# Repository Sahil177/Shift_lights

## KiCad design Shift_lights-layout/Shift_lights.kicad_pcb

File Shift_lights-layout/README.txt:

There are two files in this folder of interest. The Shift_lights.pro which u can open in Kicad to view the full PCB layout and LED-PCB_dimentions.pdf to get detailed schematics on the layout

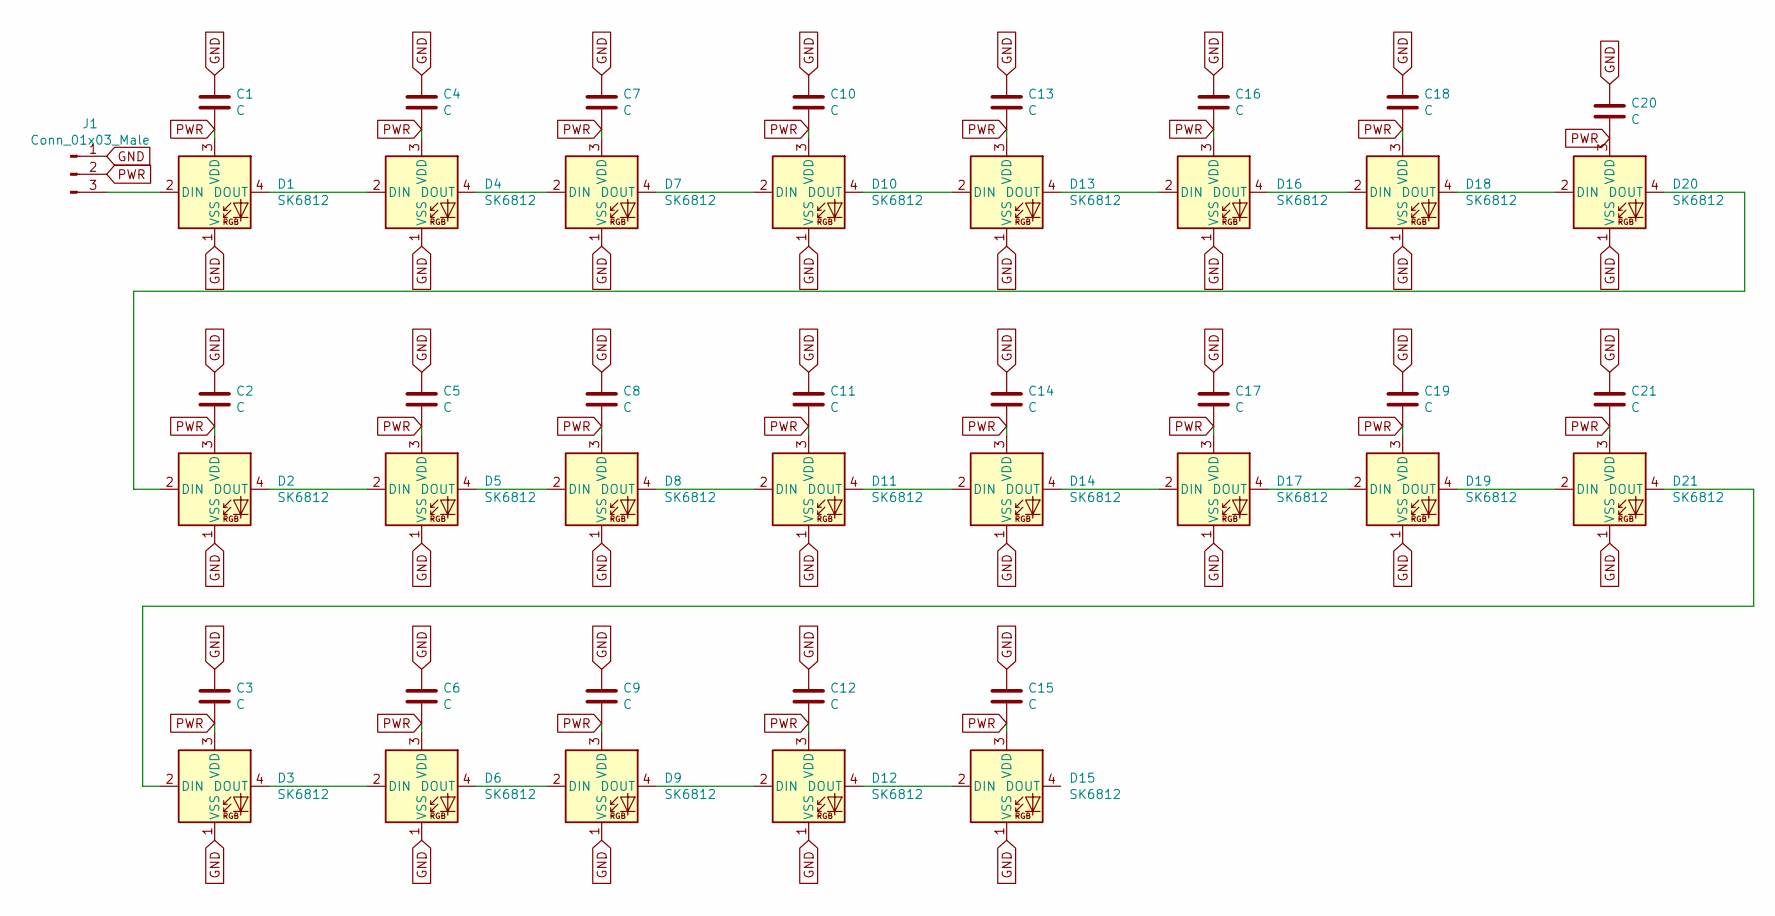
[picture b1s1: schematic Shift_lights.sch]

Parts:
C1, C2, C3, C4, C5, C6, C7, C8, C9, C10, C11, C12, C13, C14, C15, C16, C17, C18, C19, C20, C21: C; C0603C105K8PACTU
D1, D2, D3, D4, D5, D6, D7, D8, D9, D10, D11, D12, D13, D14, D15, D16, D17, D18, D19, D20, D21: SK6812; LED_SK6812_PLCC4_5.0x5.0mm_P3.2mm
J1: Conn_01x03_Male; 3_pin_connector

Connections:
GND: C1.1, C2.1, C3.1, C4.1, C5.1, C6.1, C7.1, C8.1, C9.1, C10.1, C11.1, C12.1, C13.1, C14.1, C15.1, C16.1, C17.1, C18.1, C19.1, C20.1, C21.1, D1.1 (VSS), D2.1 (VSS), D3.1 (VSS), D4.1 (VSS), D5.1 (VSS), D6.1 (VSS), D7.1 (VSS), D8.1 (VSS), D9.1 (VSS), D10.1 (VSS), D11.1 (VSS), D12.1 (VSS), D13.1 (VSS), D14.1 (VSS), D15.1 (VSS), D16.1 (VSS), D17.1 (VSS), D18.1 (VSS), D19.1 (VSS), D20.1 (VSS), D21.1 (VSS), J1.1
unnamed: D1.2 (DIN), J1.3
unnamed: D1.4 (DOUT), D4.2 (DIN)
unnamed: D2.2 (DIN), D20.4 (DOUT)
unnamed: D2.4 (DOUT), D5.2 (DIN)
unnamed: D3.4 (DOUT), D6.2 (DIN)
unnamed: D4.4 (DOUT), D7.2 (DIN)
unnamed: D5.4 (DOUT), D8.2 (DIN)
unnamed: D6.4 (DOUT), D9.2 (DIN)
unnamed: D7.4 (DOUT), D10.2 (DIN)
unnamed: D10.4 (DOUT), D13.2 (DIN)
unnamed: D8.4 (DOUT), D11.2 (DIN)
unnamed: D11.4 (DOUT), D14.2 (DIN)
unnamed: D9.4 (DOUT), D12.2 (DIN)
unnamed: D12.4 (DOUT), D15.2 (DIN)
unnamed: D13.4 (DOUT), D16.2 (DIN)
unnamed: D14.4 (DOUT), D17.2 (DIN)
unnamed: D16.4 (DOUT), D18.2 (DIN)
unnamed: D17.4 (DOUT), D19.2 (DIN)
unnamed: D18.4 (DOUT), D20.2 (DIN)
unnamed: D19.4 (DOUT), D21.2 (DIN)
unnamed: D3.2 (DIN), D21.4 (DOUT)
PWR: C1.2, C2.2, C3.2, C4.2, C5.2, C6.2, C7.2, C8.2, C9.2, C10.2, C11.2, C12.2, C13.2, C14.2, C15.2, C16.2, C17.2, C18.2, C19.2, C20.2, C21.2, D1.3 (VDD), D2.3 (VDD), D3.3 (VDD), D4.3 (VDD), D5.3 (VDD), D6.3 (VDD), D7.3 (VDD), D8.3 (VDD), D9.3 (VDD), D10.3 (VDD), D11.3 (VDD), D12.3 (VDD), D13.3 (VDD), D14.3 (VDD), D15.3 (VDD), D16.3 (VDD), D17.3 (VDD), D18.3 (VDD), D19.3 (VDD), D20.3 (VDD), D21.3 (VDD), J1.2

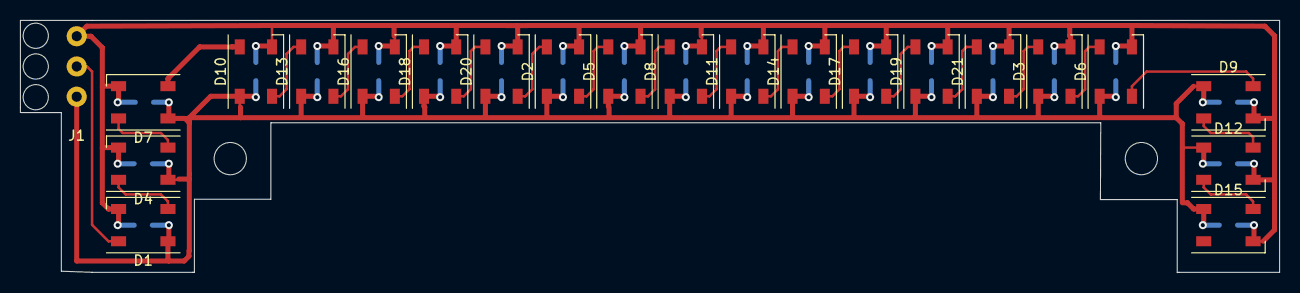
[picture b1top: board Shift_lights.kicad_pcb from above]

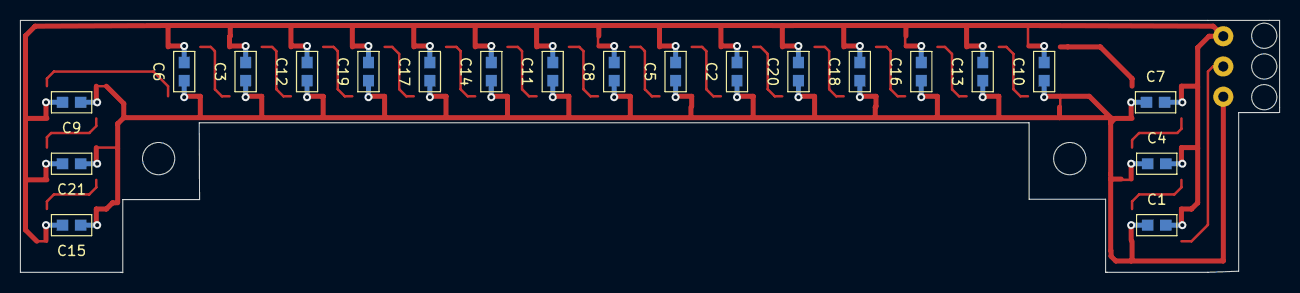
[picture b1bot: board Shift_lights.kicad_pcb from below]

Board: 2 copper layers, 125.0 x 25.0 mm, 43 parts (21 on the bottom side), 23 nets.

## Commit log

2021-10-31 Project added
